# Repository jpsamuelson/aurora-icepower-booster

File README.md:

# Aurora DSP ICEpower Booster

**6-Channel Balanced Audio Interface** — Aurora FreeDSP → ICEpower Amplifier Modules

This board sits between an **Aurora FreeDSP DSP processor** and six **ICEpower Class-D amplifier modules**. It receives 6 balanced audio signals from the DSP, applies adjustable gain (0–11.3 dB), protects the signals, and outputs them as balanced XLR signals.

---

## Features

- **6 identical channels** — balanced XLR input & output
- **LM4562 low-noise dual op-amps** — THD+N 0.00003%, 2.7 nV/√Hz
- **0–11.3 dB gain** in 8 steps via 3-bit DIP switch per channel
- **100 ms power-on muting** — BSS138 MOSFET chain prevents pop noise
- **Remote enable** via 3.5mm jack (Aurora FreeDSP compatible)
- **Full ESD protection** — PESD5V0S1BL on all signal I/O, SMBJ15CA on remote
- **Isolated power supply** — TRACO TEL5-2422 DC/DC → ADP7118/ADP7182 LDOs (±11V)
- **JLCPCB-ready** — 2-layer FR-4, all components LCSC-available

---

## Specifications

| Parameter | Value |
|-----------|-------|
| Channels | 6 (identical) |
| Input | 6× XLR Female, Pin 2 = Hot, Pin 3 = Cold, Pin 1 = GND |
| Output | 6× XLR Male, Pin 2 = Hot, Pin 3 = Cold, Pin 1 = GND |
| Power Supply | 24V DC (Barrel Jack) |
| Op-Amp Supply | ±11V (low-noise LDO) |
| Gain Range | 0 dB to +11.3 dB (8 steps via DIP switch) |
| Input Impedance | ~10 kΩ balanced |
| Output Impedance | ~47Ω (series R) |
| Input CMRR | ~62 dB (4× 10kΩ 0.1% metal film) |
| SNR Target | > 100 dB |
| THD+N Target | < 0.01% @ 1 kHz |
| Remote Interface | KH-PJ-320EA-5P-SMT 3.5mm jack (Aurora FreeDSP Custom Out) |
| Manufacturing | JLCPCB, 2-Layer, FR-4, HASL, 145.6 × 200 mm |

---

## System Overview

```mermaid
graph LR
    DSP["Aurora FreeDSP\n(6× XLR Out)"]
    BOARD["Aurora DSP\nICEpower Booster"]
    AMP1["ICEpower #1"]
    AMP2["ICEpower #2"]
    AMP3["ICEpower #3"]
    AMP4["ICEpower #4"]
    AMP5["ICEpower #5"]
    AMP6["ICEpower #6"]
    PSU["24V DC\nPower Supply"]
    REMOTE["FreeDSP\nRemote Out"]

    DSP -->|"CH1 XLR Balanced"| BOARD
    DSP -->|"CH2 XLR Balanced"| BOARD
    DSP -->|"CH3 XLR Balanced"| BOARD
    DSP -->|"CH4 XLR Balanced"| BOARD
    DSP -->|"CH5 XLR Balanced"| BOARD
    DSP -->|"CH6 XLR Balanced"| BOARD
    PSU -->|"24V"| BOARD
    REMOTE -->|"3.5mm Enable"| BOARD
    BOARD -->|"CH1 +Gain"| AMP1
    BOARD -->|"CH2 +Gain"| AMP2
    BOARD -->|"CH3 +Gain"| AMP3
    BOARD -->|"CH4 +Gain"| AMP4
    BOARD -->|"CH5 +Gain"| AMP5
    BOARD -->|"CH6 +Gain"| AMP6
```

---

## Signal Chain Overview

All 6 channels are **identical**. Each channel consists of 5 stages:

```mermaid
flowchart LR
    XIN["XLR IN\nJ3–J8"]
    ESD1["ESD Protection\nInput"]
    EMI["EMI Filter\n47Ω + 100pF"]
    DC["DC Blocking\n2.2µF C0G"]
    DIFF["Diff Receiver\nLM4562 Unit A"]
    GAIN["Gain Stage\nLM4562 Unit B"]
    MUTE["Muting\nBSS138"]
    DRV["Balanced Driver\nLM4562 (2nd IC)"]
    ZOB["Zobel\n10Ω + 100nF"]
    ESD2["ESD Protection\nOutput"]
    XOUT["XLR OUT\nJ9–J14"]

    XIN --> ESD1 --> EMI --> DC --> DIFF --> GAIN --> MUTE --> DRV --> ZOB --> ESD2 --> XOUT
```

| Stage | Function | Key Components |
|-------|----------|---------------|
| 1. ESD & EMI Filter | Overvoltage protection + RF filtering | PESD5V0S1BL, 47Ω + 100pF, 2.2µF C0G DC blocking |
| 2. Diff Receiver | Balanced → single-ended, CMRR ~62 dB | LM4562 Unit A, 4× 10kΩ 0.1% |
| 3. Gain Stage | Inverting amp, 0–11.3 dB adjustable | LM4562 Unit B, DIP switch + 3 parallel R |
| 4. Muting | Power-on pop suppression, τ = 100 ms | BSS138 N-MOSFET, RC timing |
| 5. Balanced Driver | Single-ended → balanced output | LM4562 (buffer + inverter), 47Ω series R, Zobel network |

**→ [Full signal chain documentation with schematics and formulas](docs/signal-chain.md)**

---

## Gain Configuration

| SW Pos 1 (30kΩ) | SW Pos 2 (15kΩ) | SW Pos 3 (7.5kΩ) | Gain (dB) |
|:---:|:---:|:---:|---:|
| OFF | OFF | OFF | 0.0 dB |
| OFF | OFF | ON | +2.5 dB |
| OFF | ON | OFF | +4.4 dB |
| OFF | ON | ON | +6.0 dB |
| ON | OFF | OFF | +7.4 dB |
| ON | OFF | ON | +8.5 dB |
| ON | ON | OFF | +9.5 dB |
| ON | ON | ON | **+11.3 dB** |

$$G = \frac{R_f}{R_{in,eff}} \quad\text{with}\quad R_{in,eff} = R_{base} \parallel R_{pos1} \parallel R_{pos2} \parallel R_{pos3}$$

**→ [Full gain configuration details](docs/gain-configuration.md)**

---

## PCB Layout

| Parameter | Value |
|-----------|-------|
| Board Size | 145.6 × 200 mm |
| Layers | 2 (F.Cu + B.Cu) |
| Footprints | 269 |
| Nets | 135 in 5 net classes |
| Routing | Freerouting v2.0.1 — 1543 segments + 476 vias |
| GND Zones | F.Cu (solid connect) + B.Cu (thermal relief) |
| DRC | 0 Errors, 0 Unconnected, 198 Warnings (cosmetic) |

| Net Class | Nets | Track Width | Clearance |
|-----------|------|-------------|-----------|
| Default | 62 | 0.25 mm | 0.2 mm |
| Audio_Input | 30 | 0.3 mm | 0.25 mm |
| Audio_Output | 36 | 0.5 mm | 0.2 mm |
| Audio_Power | 0 | 0.8 mm | 0.2 mm |
| Power | 7 | 0.5 mm | 0.2 mm |

**→ [PCB layout details & DRC breakdown](docs/pcb-layout.md)**

---

## Manufacturing

Production files are ready in the `production/` directory:

- **Gerber + Drill** — `production/gerber/` (JLCPCB format, Protel extensions, tented vias)
- **BOM + Placement** — `production/assembly/` (JLCPCB SMT assembly format)

---

## Validation

| Method | Checks | Result |
|--------|--------|--------|
| **Method 1** — OrcadPCB2 netlist, component-centric | 85/85 | ✅ |
| **Method 2** — KiCad-native netlist, net-centric (pintype/pinfunction) | 177/177 | ✅ |

> All component references, net names, and pin assignments in the documentation were extracted directly from the verified KiCad netlist and are sufficient to fully rebuild the schematic without the `.kicad_sch` file.

---

## Documentation

| Document | Description |
|----------|-------------|
| **[Signal Chain](docs/signal-chain.md)** | Detailed 5-stage signal path with Mermaid diagrams, formulas, and per-stage component tables |
| **[Power Supply](docs/power-supply.md)** | DC/DC converter, LDOs, ferrite beads, decoupling architecture |
| **[Muting & Remote Control](docs/muting-and-remote.md)** | Remote enable logic, muting timing, SPDT switch modes |
| **[Gain Configuration](docs/gain-configuration.md)** | DIP switch table, gain formula, per-channel resistor mapping |
| **[Component Reference](docs/component-reference.md)** | Complete BOM with all 242 symbols: R, C, D, J, SW, Q, U, FB |
| **[Schematic Rebuild Guide](docs/schematic-rebuild-guide.md)** | Step-by-step wiring instructions + full 6-channel component mapping |
| **[PCB Layout](docs/pcb-layout.md)** | Net classes, DRC status, routing details |
| **[Research: Balanced Audio ICs](docs/research/balanced-audio-ic-comparison.md)** | THAT1240, DRV135, SSM2143, LM4562 comparison & JLCPCB availability |
| **[Research: THT Precision Components](docs/research/tht-precision-components.md)** | 0.1% resistors, C0G capacitors, THT sourcing guide |

---

## Project Structure

This project is **self-contained** — all footprints and 3D models are included locally.

```
├── aurora-dsp-icepower-booster.kicad_pro   # Project
├── aurora-dsp-icepower-booster.kicad_sch   # Schematic
├── aurora-dsp-icepower-booster.kicad_pcb   # PCB Layout
├── aurora-dsp-icepower-booster.kicad_sym   # Local symbols
├── aurora-dsp-icepower-booster.kicad_dru   # Custom design rules
├── footprints.pretty/                      # 21 footprints (local)
│   └── 3dshapes/                           # 19 STEP 3D models
├── production/
│   ├── gerber/                             # Manufacturing data
│   └── assembly/                           # BOM + placement data
├── docs/                                   # Detailed documentation
│   ├── signal-chain.md
│   ├── power-supply.md
│   ├── muting-and-remote.md
│   ├── gain-configuration.md
│   ├── component-reference.md
│   ├── schematic-rebuild-guide.md
│   ├── pcb-layout.md
│   └── research/
│       ├── balanced-audio-ic-comparison.md
│       └── tht-precision-components.md
└── scripts/                                # Build & validation scripts
```

---

*Schematic: KiCad 9 — `aurora-dsp-icepower-booster.kicad_sch`*
*Manufacturing: JLCPCB 2-Layer FR-4 HASL — Gerber files in `production/gerber/`*

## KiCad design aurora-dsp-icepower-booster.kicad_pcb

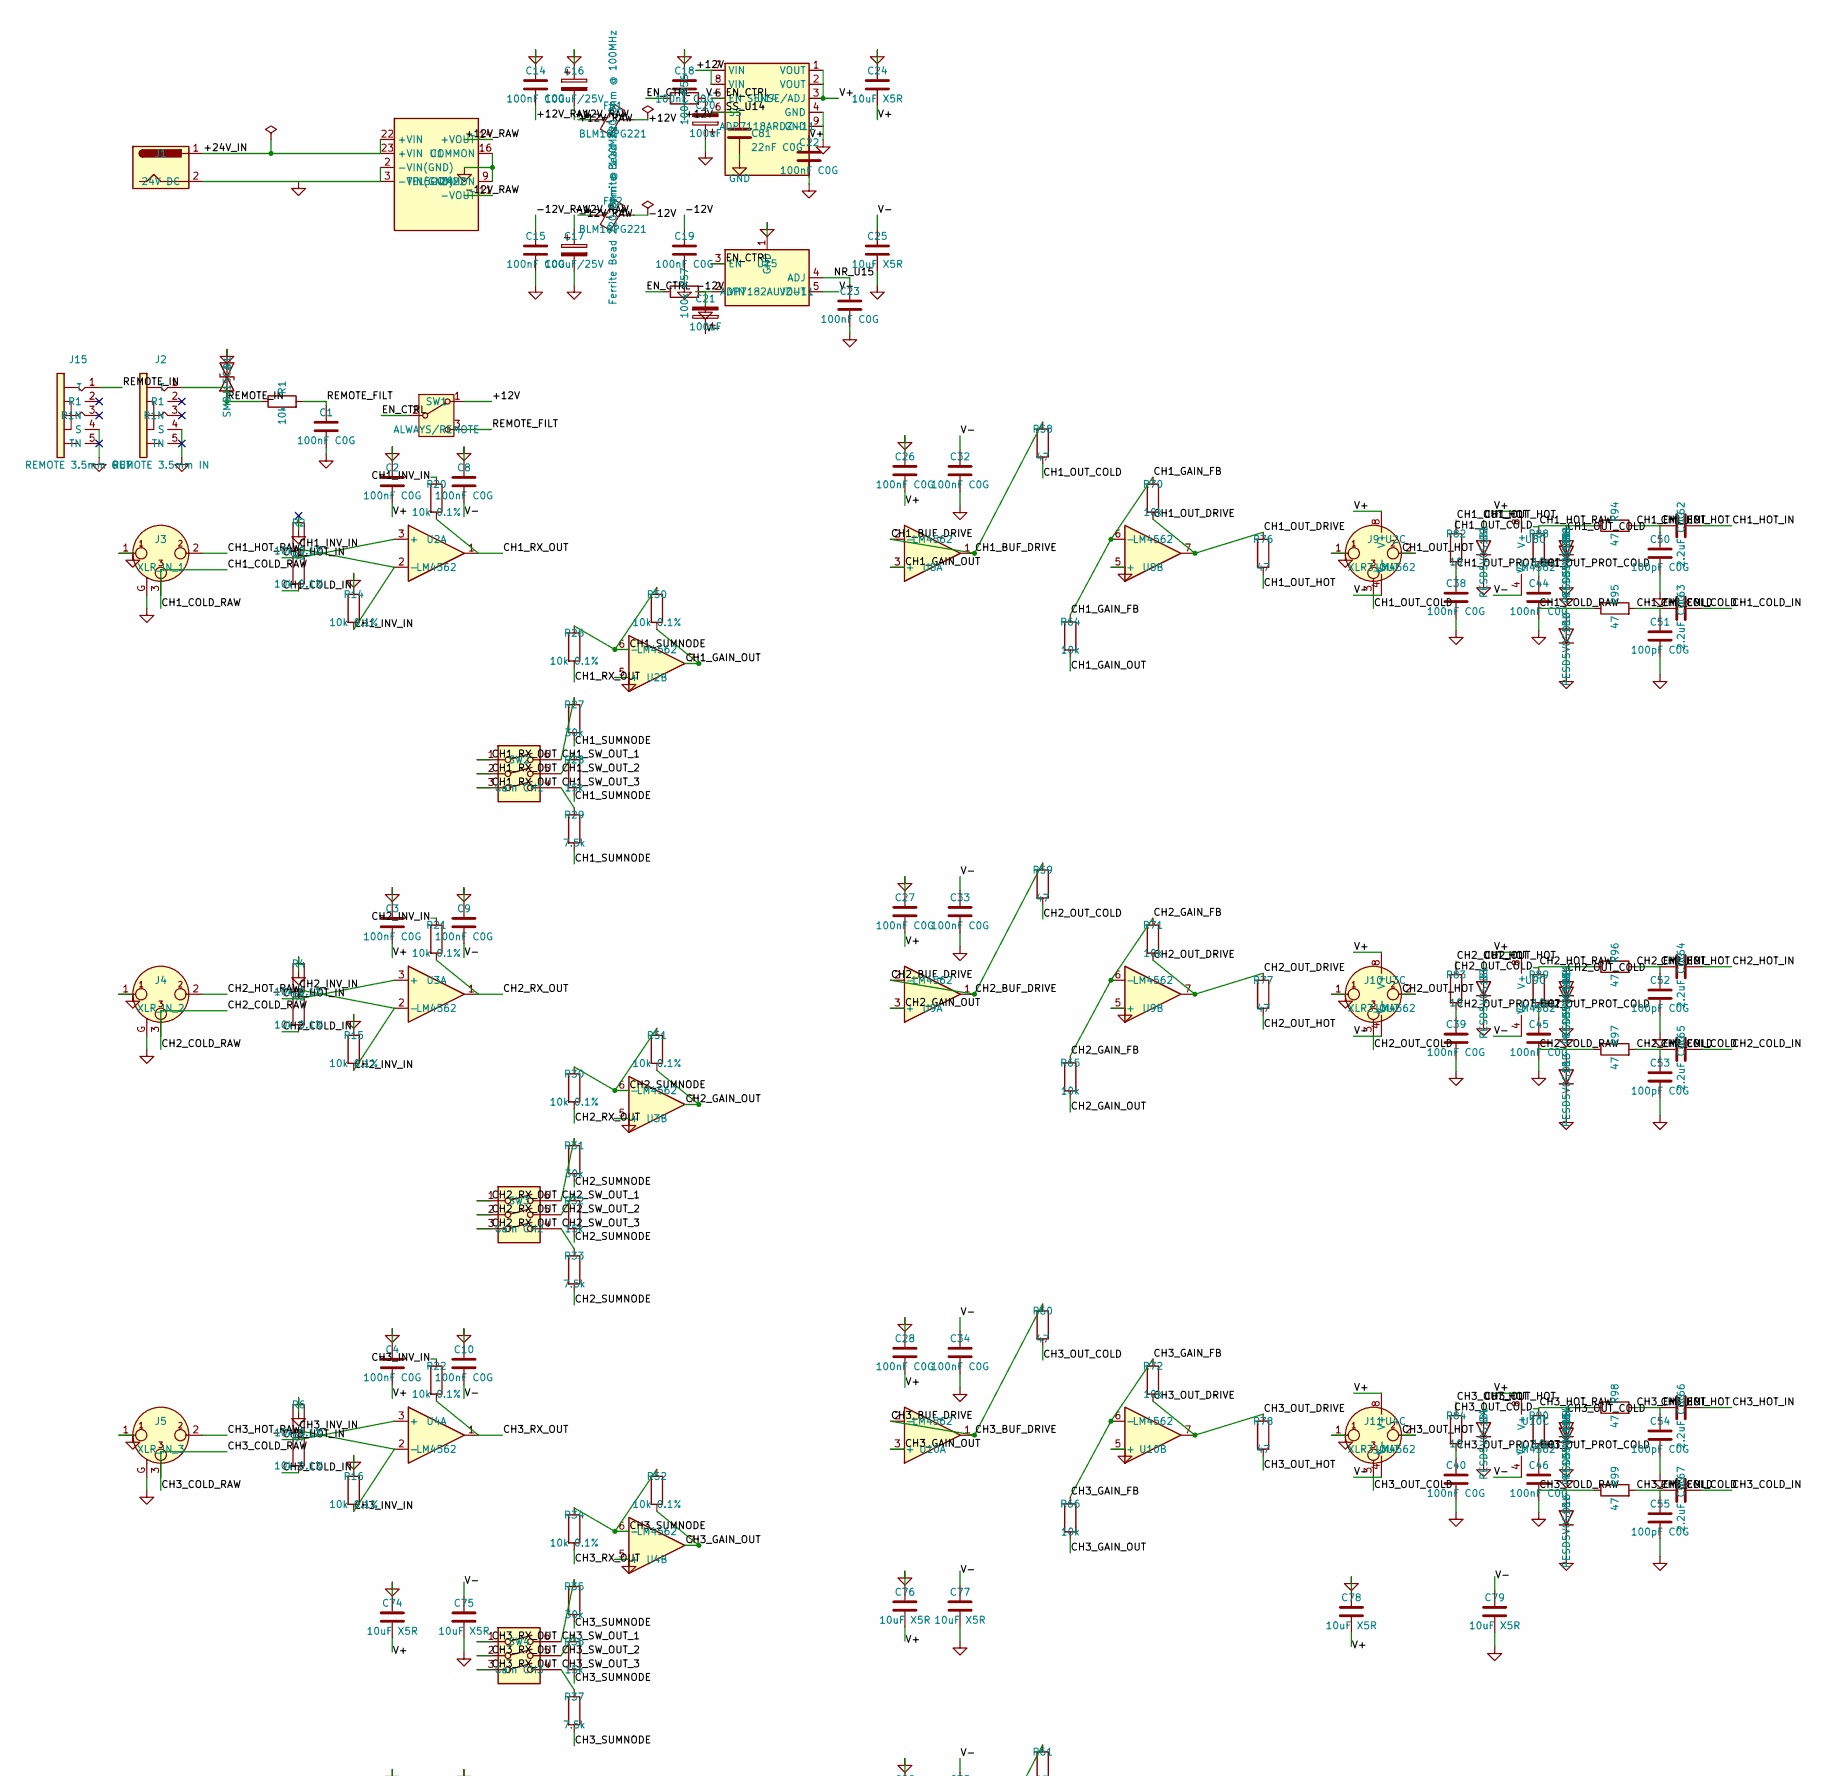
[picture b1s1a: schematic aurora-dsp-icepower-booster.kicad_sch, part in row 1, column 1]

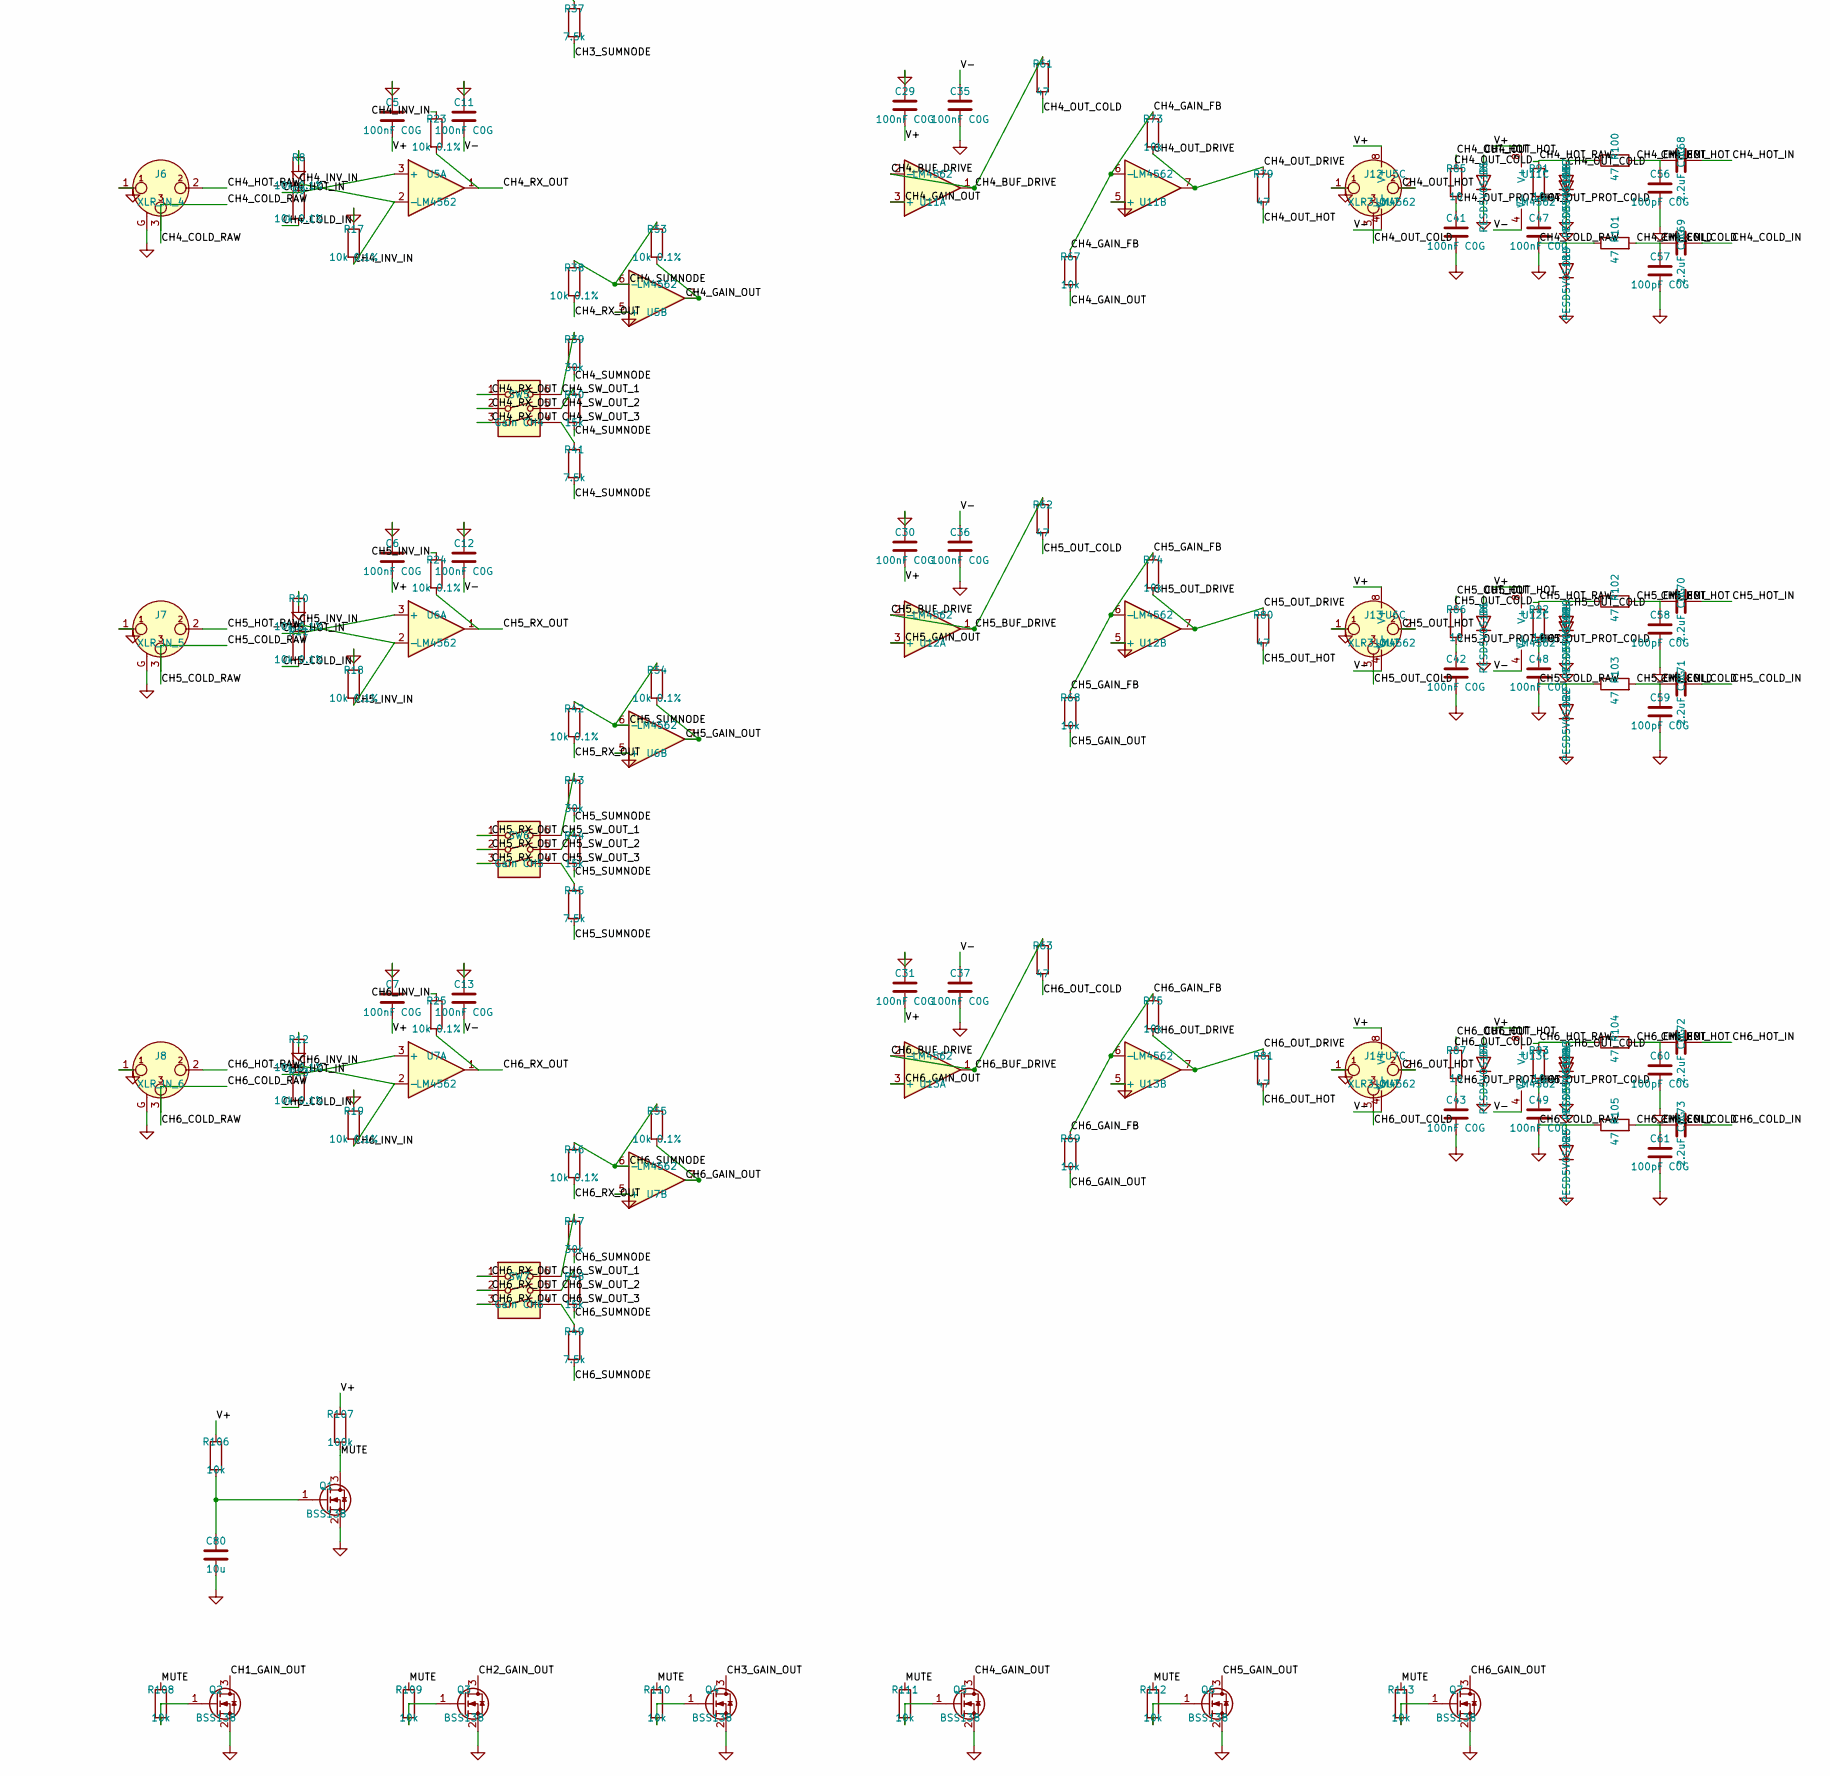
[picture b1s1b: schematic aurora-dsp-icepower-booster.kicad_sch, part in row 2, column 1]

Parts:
C1, C2, C3, C4, C5, C6, C7, C8, C9, C10, C11, C12, C13, C14, C15, C18, C19, C22, C23, C26, C27, C28, C29, C30, C31, C32, C33, C34, C35, C36, C37, C38, C39, C40, C41, C42, C43, C44, C45, C46, C47, C48, C49: 100nF C0G; C_0805_2012Metric
C16, C17: 100uF/25V; C_1210_3225Metric
C20, C21: 100uF; C_1210_3225Metric
C24, C25, C74, C75, C76, C77, C78, C79: 10uF X5R; C_0805_2012Metric
C50, C51, C52, C53, C54, C55, C56, C57, C58, C59, C60, C61: 100pF C0G; C_0805_2012Metric
C62, C63, C64, C65, C66, C67, C68, C69, C70, C71, C72, C73: 2.2uF C0G; C_1206_3216Metric
C80: 10u; C_0805_2012Metric
C81: 22nF C0G; C_0402_1005Metric
D1: SMBJ15CA; D_SMB
D2, D3, D4, D5, D6, D7, D8, D9, D10, D11, D12, D13, D14, D15, D16, D17, D18, D19, D20, D21, D22, D23, D24, D25: PESD5V0S1BL; D_SOD-323
FB1, FB2: BLM18PG221; L_0805_2012Metric
J1: 24V DC; BarrelJack_Horizontal
J2: REMOTE 3.5mm IN; AUDIO-SMD_KH-PJ-320EA-5P-SMT; LCSC C5123132
J3: XLR_IN_1; Jack_XLR_Neutrik_NC3FBH2_Horizontal
J4: XLR_IN_2; Jack_XLR_Neutrik_NC3FBH2_Horizontal
J5: XLR_IN_3; Jack_XLR_Neutrik_NC3FBH2_Horizontal
J6: XLR_IN_4; Jack_XLR_Neutrik_NC3FBH2_Horizontal
J7: XLR_IN_5; Jack_XLR_Neutrik_NC3FBH2_Horizontal
J8: XLR_IN_6; Jack_XLR_Neutrik_NC3FBH2_Horizontal
J9, J10, J11, J12, J13, J14: XLR3_OUT; Jack_XLR_Neutrik_NC3MBH_Horizontal
J15: REMOTE 3.5mm OUT; AUDIO-SMD_KH-PJ-320EA-5P-SMT; LCSC C5123132
Q1, Q2, Q3, Q4, Q5, Q6, Q7: BSS138; SOT-23
R1, R64, R65, R66, R67, R68, R69, R70, R71, R72, R73, R74, R75, R106, R108, R109, R110, R111, R112, R113: 10k; R_0805_2012Metric
R2, R3, R4, R5, R6, R7, R8, R9, R10, R11, R12, R13, R14, R15, R16, R17, R18, R19, R20, R21, R22, R23, R24, R25, R26, R30, R34, R38, R42, R46, R50, R51, R52, R53, R54, R55: 10k 0.1%; R_0805_2012Metric
R27, R31, R35, R39, R43, R47: 30k; R_0805_2012Metric
R28, R32, R36, R40, R44, R48: 15k; R_0805_2012Metric
R29, R33, R37, R41, R45, R49: 7.5k; R_0805_2012Metric
R56, R57, R107: 100k; R_0805_2012Metric
R58, R59, R60, R61, R62, R63, R76, R77, R78, R79, R80, R81, R94, R95, R96, R97, R98, R99, R100, R101, R102, R103, R104, R105: 47; R_0805_2012Metric
R82, R83, R84, R85, R86, R87, R88, R89, R90, R91, R92, R93: 10; R_0805_2012Metric
SW1: ALWAYS/REMOTE; SW_E-Switch_EG1224_SPDT_Angled
SW2: Gain CH1; SW_DIP_SPSTx03_Slide_Omron_A6S-310x_W8.9mm_P2.54mm
SW3: Gain CH2; SW_DIP_SPSTx03_Slide_Omron_A6S-310x_W8.9mm_P2.54mm
SW4: Gain CH3; SW_DIP_SPSTx03_Slide_Omron_A6S-310x_W8.9mm_P2.54mm
SW5: Gain CH4; SW_DIP_SPSTx03_Slide_Omron_A6S-310x_W8.9mm_P2.54mm
SW6: Gain CH5; SW_DIP_SPSTx03_Slide_Omron_A6S-310x_W8.9mm_P2.54mm
SW7: Gain CH6; SW_DIP_SPSTx03_Slide_Omron_A6S-310x_W8.9mm_P2.54mm
U1: TEL5-2422; TEL5_DUAL_TRP
U2, U3, U4, U5, U6, U7, U8, U9, U10, U11, U12, U13: LM4562; SOIC-8_3.9x4.9mm_P1.27mm
U14: ADP7118ARDZ-11; SOIC127P600X175-9N
U15: ADP7182AUJZ-11; SOT-23-5

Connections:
/+12V: C18.2, FB1.2, SW1.1 (A), U14.7 (VIN), U14.8 (VIN)
/+12V_RAW: C14.2, C16.2, FB1.1, U1.14 (+VOUT)
/+24V_IN: J1.1, U1.22 (+VIN), U1.23 (+VIN)
/-12V: C19.1, FB2.2, U15.2 (VIN)
/-12V_RAW: C15.1, C17.1, FB2.1, U1.11 (-VOUT)
/CH1_BUF_DRIVE: R58.1, U8.1, U8.2 (-)
/CH1_COLD_IN: C63.2, R3.2
/CH1_COLD_RAW: D10.2 (A), J3.3, R95.1
/CH1_EMI_COLD: C51.1, C63.1, R95.2
/CH1_EMI_HOT: C50.1, C62.1, R94.2
/CH1_GAIN_FB: R64.1, R70.1, U8.6 (-)
/CH1_GAIN_OUT: Q2.3 (D), R50.2, R64.2, U2.7, U8.3 (+)
/CH1_HOT_IN: C62.2, R2.2, U2.3 (+)
/CH1_HOT_RAW: D8.2 (A), J3.2, R94.1
/CH1_INV_IN: R3.1, R14.2, R20.1, U2.2 (-)
/CH1_OUT_COLD: D9.2 (A), J9.3, R58.2, R88.1
/CH1_OUT_DRIVE: R70.2, R76.1, U8.7
/CH1_OUT_HOT: D2.2 (A), J9.2, R76.2, R82.1
/CH1_OUT_PROT_COLD: C44.1, R88.2
/CH1_OUT_PROT_HOT: C38.1, R82.2
/CH1_RX_OUT: R20.2, R26.2, SW2.1, SW2.2, SW2.3, U2.1
/CH1_SUMNODE: R26.1, R27.2, R28.2, R29.2, R50.1, U2.6 (-)
/CH1_SW_OUT_1: R27.1, SW2.6
/CH1_SW_OUT_2: R28.1, SW2.5
/CH1_SW_OUT_3: R29.1, SW2.4
/CH2_BUF_DRIVE: R59.1, U9.1, U9.2 (-)
/CH2_COLD_IN: C65.2, R5.2
/CH2_COLD_RAW: D13.2 (A), J4.3, R97.1
/CH2_EMI_COLD: C53.1, C65.1, R97.2
/CH2_EMI_HOT: C52.1, C64.1, R96.2
/CH2_GAIN_FB: R65.1, R71.1, U9.6 (-)
/CH2_GAIN_OUT: Q3.3 (D), R51.2, R65.2, U3.7, U9.3 (+)
/CH2_HOT_IN: C64.2, R4.2, U3.3 (+)
/CH2_HOT_RAW: D11.2 (A), J4.2, R96.1
/CH2_INV_IN: R5.1, R15.2, R21.1, U3.2 (-)
/CH2_OUT_COLD: D12.2 (A), J10.3, R59.2, R89.1
/CH2_OUT_DRIVE: R71.2, R77.1, U9.7
/CH2_OUT_HOT: D3.2 (A), J10.2, R77.2, R83.1
/CH2_OUT_PROT_COLD: C45.1, R89.2
/CH2_OUT_PROT_HOT: C39.1, R83.2
/CH2_RX_OUT: R21.2, R30.2, SW3.1, SW3.2, SW3.3, U3.1
/CH2_SUMNODE: R30.1, R31.2, R32.2, R33.2, R51.1, U3.6 (-)
/CH2_SW_OUT_1: R31.1, SW3.6
/CH2_SW_OUT_2: R32.1, SW3.5
/CH2_SW_OUT_3: R33.1, SW3.4
/CH3_BUF_DRIVE: R60.1, U10.1, U10.2 (-)
/CH3_COLD_IN: C67.2, R7.2
/CH3_COLD_RAW: D16.2 (A), J5.3, R99.1
/CH3_EMI_COLD: C55.1, C67.1, R99.2
/CH3_EMI_HOT: C54.1, C66.1, R98.2
/CH3_GAIN_FB: R66.1, R72.1, U10.6 (-)
/CH3_GAIN_OUT: Q4.3 (D), R52.2, R66.2, U4.7, U10.3 (+)
/CH3_HOT_IN: C66.2, R6.2, U4.3 (+)
/CH3_HOT_RAW: D14.2 (A), J5.2, R98.1
/CH3_INV_IN: R7.1, R16.2, R22.1, U4.2 (-)
/CH3_OUT_COLD: D15.2 (A), J11.3, R60.2, R90.1
/CH3_OUT_DRIVE: R72.2, R78.1, U10.7
/CH3_OUT_HOT: D4.2 (A), J11.2, R78.2, R84.1
/CH3_OUT_PROT_COLD: C46.1, R90.2
/CH3_OUT_PROT_HOT: C40.1, R84.2
/CH3_RX_OUT: R22.2, R34.2, SW4.1, SW4.2, SW4.3, U4.1
/CH3_SUMNODE: R34.1, R35.2, R36.2, R37.2, R52.1, U4.6 (-)
/CH3_SW_OUT_1: R35.1, SW4.6
/CH3_SW_OUT_2: R36.1, SW4.5
/CH3_SW_OUT_3: R37.1, SW4.4
/CH4_BUF_DRIVE: R61.1, U11.1, U11.2 (-)
/CH4_COLD_IN: C69.2, R9.2
/CH4_COLD_RAW: D19.2 (A), J6.3, R101.1
/CH4_EMI_COLD: C57.1, C69.1, R101.2
/CH4_EMI_HOT: C56.1, C68.1, R100.2
/CH4_GAIN_FB: R67.1, R73.1, U11.6 (-)
/CH4_GAIN_OUT: Q5.3 (D), R53.2, R67.2, U5.7, U11.3 (+)
/CH4_HOT_IN: C68.2, R8.2, U5.3 (+)
/CH4_HOT_RAW: D17.2 (A), J6.2, R100.1
/CH4_INV_IN: R9.1, R17.2, R23.1, U5.2 (-)
/CH4_OUT_COLD: D18.2 (A), J12.3, R61.2, R91.1
/CH4_OUT_DRIVE: R73.2, R79.1, U11.7
/CH4_OUT_HOT: D5.2 (A), J12.2, R79.2, R85.1
/CH4_OUT_PROT_COLD: C47.1, R91.2
/CH4_OUT_PROT_HOT: C41.1, R85.2
/CH4_RX_OUT: R23.2, R38.2, SW5.1, SW5.2, SW5.3, U5.1
/CH4_SUMNODE: R38.1, R39.2, R40.2, R41.2, R53.1, U5.6 (-)
/CH4_SW_OUT_1: R39.1, SW5.6
/CH4_SW_OUT_2: R40.1, SW5.5
/CH4_SW_OUT_3: R41.1, SW5.4
/CH5_BUF_DRIVE: R62.1, U12.1, U12.2 (-)
/CH5_COLD_IN: C71.2, R11.2
/CH5_COLD_RAW: D22.2 (A), J7.3, R103.1
/CH5_EMI_COLD: C59.1, C71.1, R103.2
/CH5_EMI_HOT: C58.1, C70.1, R102.2
/CH5_GAIN_FB: R68.1, R74.1, U12.6 (-)
/CH5_GAIN_OUT: Q6.3 (D), R54.2, R68.2, U6.7, U12.3 (+)
/CH5_HOT_IN: C70.2, R10.2, U6.3 (+)
/CH5_HOT_RAW: D20.2 (A), J7.2, R102.1
/CH5_INV_IN: R11.1, R18.2, R24.1, U6.2 (-)
/CH5_OUT_COLD: D21.2 (A), J13.3, R62.2, R92.1
/CH5_OUT_DRIVE: R74.2, R80.1, U12.7
/CH5_OUT_HOT: D6.2 (A), J13.2, R80.2, R86.1
/CH5_OUT_PROT_COLD: C48.1, R92.2
/CH5_OUT_PROT_HOT: C42.1, R86.2
/CH5_RX_OUT: R24.2, R42.2, SW6.1, SW6.2, SW6.3, U6.1
/CH5_SUMNODE: R42.1, R43.2, R44.2, R45.2, R54.1, U6.6 (-)
/CH5_SW_OUT_1: R43.1, SW6.6
/CH5_SW_OUT_2: R44.1, SW6.5
/CH5_SW_OUT_3: R45.1, SW6.4
/CH6_BUF_DRIVE: R63.1, U13.1, U13.2 (-)
/CH6_COLD_IN: C73.2, R13.2
/CH6_COLD_RAW: D25.2 (A), J8.3, R105.1
/CH6_EMI_COLD: C61.1, C73.1, R105.2
/CH6_EMI_HOT: C60.1, C72.1, R104.2
/CH6_GAIN_FB: R69.1, R75.1, U13.6 (-)
/CH6_GAIN_OUT: Q7.3 (D), R55.2, R69.2, U7.7, U13.3 (+)
/CH6_HOT_IN: C72.2, R12.2, U7.3 (+)
/CH6_HOT_RAW: D23.2 (A), J8.2, R104.1
/CH6_INV_IN: R13.1, R19.2, R25.1, U7.2 (-)
/CH6_OUT_COLD: D24.2 (A), J14.3, R63.2, R93.1
/CH6_OUT_DRIVE: R75.2, R81.1, U13.7
/CH6_OUT_HOT: D7.2 (A), J14.2, R81.2, R87.1
/CH6_OUT_PROT_COLD: C49.1, R93.2
/CH6_OUT_PROT_HOT: C43.1, R87.2
/CH6_RX_OUT: R25.2, R46.2, SW7.1, SW7.2, SW7.3, U7.1
/CH6_SUMNODE: R46.1, R47.2, R48.2, R49.2, R55.1, U7.6 (-)
/CH6_SW_OUT_1: R47.1, SW7.6
/CH6_SW_OUT_2: R48.1, SW7.5
/CH6_SW_OUT_3: R49.1, SW7.4
/EN_CTRL: R56.1, R57.1, SW1.2 (B), U14.5 (EN), U15.3 (EN)
/MUTE: Q1.3 (D), R107.2, R108.1, R109.1, R110.1, R111.1, R112.1, R113.1
/NR_U15: C23.1, U15.4 (ADJ)
/REMOTE_FILT: C1.1, R1.2, SW1.3 (C)
/REMOTE_IN: D1.1 (A1), J2.1 (T), J15.1 (T), R1.1
/SS_U14: C81.1, U14.6 (SS)
/V+: C2.2, C3.2, C4.2, C5.2, C6.2, C7.2, C20.2, C22.1, C24.2, C26.2, C27.2, C28.2, C29.2, C30.2, C31.2, C74.2, C76.2, C78.2, R56.2, R106.1, R107.1, U2.8 (V+), U3.8 (V+), U4.8 (V+), U5.8 (V+), U6.8 (V+), U7.8 (V+), U8.8 (V+), U9.8 (V+), U10.8 (V+), U11.8 (V+), U12.8 (V+), U13.8 (V+), U14.1 (VOUT), U14.2 (VOUT), U14.3 (SENSE/ADJ)
/V-: C8.2, C9.2, C10.2, C11.2, C12.2, C13.2, C21.1, C25.1, C32.1, C33.1, C34.1, C35.1, C36.1, C37.1, C75.1, C77.1, C79.1, U2.4 (V-), U3.4 (V-), U4.4 (V-), U5.4 (V-), U6.4 (V-), U7.4 (V-), U8.4 (V-), U9.4 (V-), U10.4 (V-), U11.4 (V-), U12.4 (V-), U13.4 (V-), U15.5 (VOUT)
GND: C1.2, C2.1, C3.1, C4.1, C5.1, C6.1, C7.1, C8.1, C9.1, C10.1, C11.1, C12.1, C13.1, C14.1, C15.2, C16.1, C17.2, C18.1, C19.2, C20.1, C21.2, C22.2, C23.2, C24.1, C25.2, C26.1, C27.1, C28.1, C29.1, C30.1, C31.1, C32.2, C33.2, C34.2, C35.2, C36.2, C37.2, C38.2, C39.2, C40.2, C41.2, C42.2, C43.2, C44.2, C45.2, C46.2, C47.2, C48.2, C49.2, C50.2, C51.2, C52.2, C53.2, C54.2, C55.2, C56.2, C57.2, C58.2, C59.2, C60.2, C61.2, C74.1, C75.2, C76.1, C77.2, C78.1, C79.2, C80.2, C81.2, D1.2 (A2), D2.1 (K), D3.1 (K), D4.1 (K), D5.1 (K), D6.1 (K), D7.1 (K), D8.1 (K), D9.1 (K), D10.1 (K), D11.1 (K), D12.1 (K), D13.1 (K), D14.1 (K), D15.1 (K), D16.1 (K), D17.1 (K), D18.1 (K), D19.1 (K), D20.1 (K), D21.1 (K), D22.1 (K), D23.1 (K), D24.1 (K), D25.1 (K), J1.2, J2.4 (S), J3.1, J3.G, J4.1, J4.G, J5.1, J5.G, J6.1, J6.G, J7.1, J7.G, J8.1, J8.G, J9.1, J10.1, J11.1, J12.1, J13.1, J14.1, J15.4 (S), Q1.2 (S), Q2.2 (S), Q3.2 (S), Q4.2 (S), Q5.2 (S), Q6.2 (S), Q7.2 (S), R2.1, R4.1, R6.1, R8.1, R10.1, R12.1, R14.1, R15.1, R16.1, R17.1, R18.1, R19.1, R57.2, U1.2 (-VIN(GND)), U1.3 (-VIN(GND)), U1.9 (COMMON), U1.16 (COMMON), U2.5 (+), U3.5 (+), U4.5 (+), U5.5 (+), U6.5 (+), U7.5 (+), U8.5 (+), U9.5 (+), U10.5 (+), U11.5 (+), U12.5 (+), U13.5 (+), U14.4 (GND), U14.9 (GND), U15.1 (GND)
unnamed: C80.1, Q1.1 (G), R106.2
unnamed: Q2.1 (G), R108.2
unnamed: Q3.1 (G), R109.2
unnamed: Q4.1 (G), R110.2
unnamed: Q5.1 (G), R111.2
unnamed: Q6.1 (G), R112.2
unnamed: Q7.1 (G), R113.2

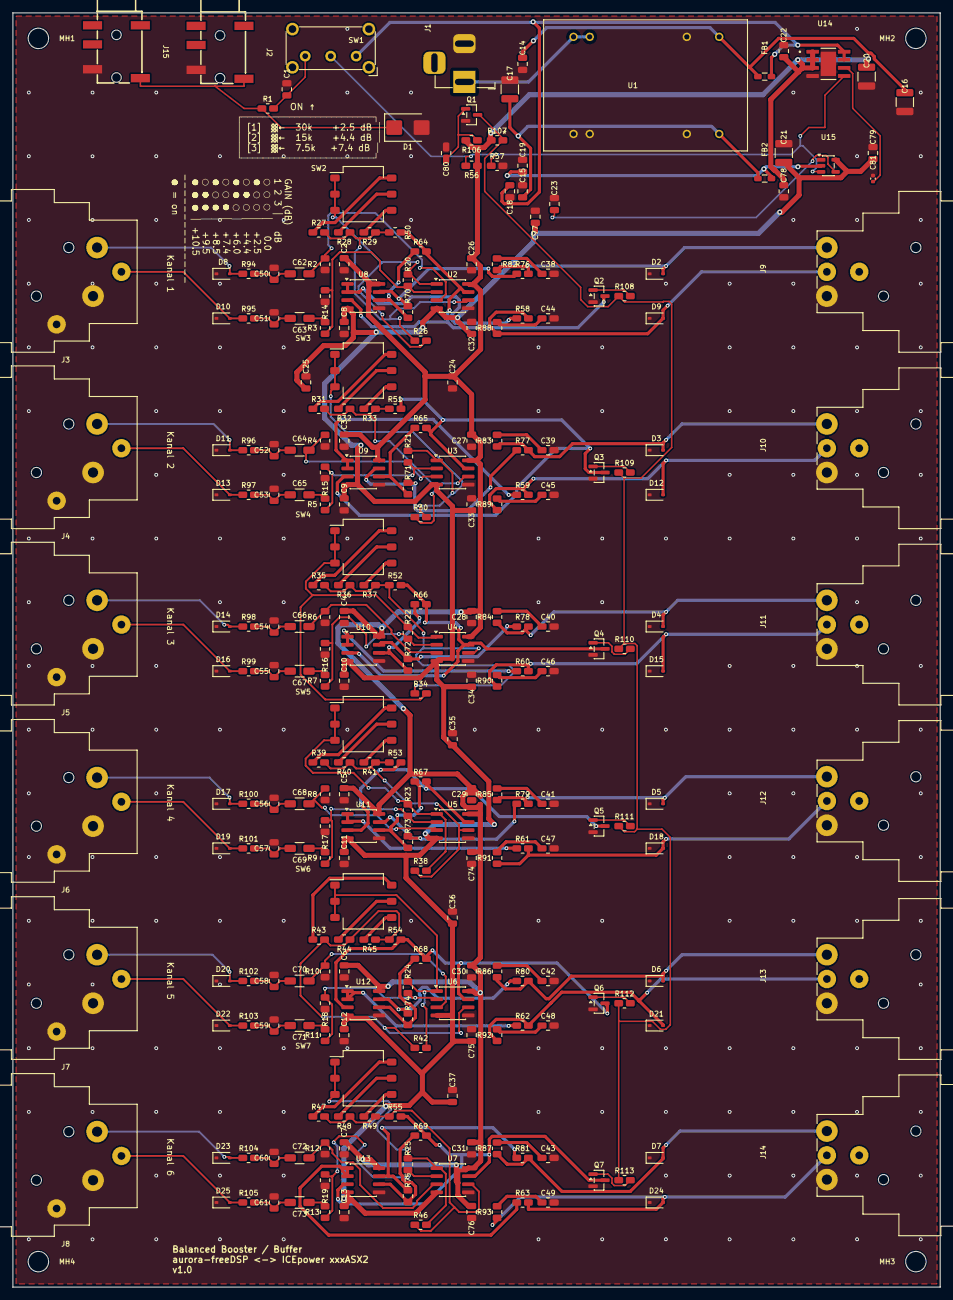
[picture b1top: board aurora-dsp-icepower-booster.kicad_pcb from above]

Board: 2 copper layers, 145.6 x 200.0 mm, 269 parts (0 on the bottom side), 141 nets.

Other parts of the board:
MH1, MH2, MH3, MH4: MountingHole; MountingHole_3.2mm_M3

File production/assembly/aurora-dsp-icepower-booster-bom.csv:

"Reference","Value","Footprint","QUANTITY"
"C1-C15,C18,C19,C22,C23,C26-C49","100nF C0G","Capacitor_SMD:C_0805_2012Metric","43"
"C16,C17","100uF/25V","Capacitor_SMD:C_1210_3225Metric","2"
"C20,C21","100uF","Capacitor_SMD:C_1210_3225Metric","2"
"C24,C25,C74-C79","10uF X5R","Capacitor_SMD:C_0805_2012Metric","8"
"C50-C61","100pF C0G","Capacitor_SMD:C_0805_2012Metric","12"
"C62-C73","2.2uF C0G","Capacitor_SMD:C_1206_3216Metric","12"
"C80","10u","Capacitor_SMD:C_0805_2012Metric","1"
"C81","22nF C0G","Capacitor_SMD:C_0402_1005Metric","1"
"D1","SMBJ15CA","Diode_SMD:D_SMB","1"
"D2-D25","PESD5V0S1BL","Diode_SMD:D_SOD-323","24"
"FB1,FB2","BLM18PG221","Inductor_SMD:L_0805_2012Metric","2"
"J1","24V DC","Connector_BarrelJack:BarrelJack_Horizontal","1"
"J2","REMOTE 3.5mm","Connector_Audio:Jack_3.5mm_Lumberg_1503_02_Horizontal","1"
"J3","XLR_IN_1","Connector_Audio:Jack_XLR_Neutrik_NC3FBH2_Horizontal","1"
"J4","XLR_IN_2","Connector_Audio:Jack_XLR_Neutrik_NC3FBH2_Horizontal","1"
"J5","XLR_IN_3","Connector_Audio:Jack_XLR_Neutrik_NC3FBH2_Horizontal","1"
"J6","XLR_IN_4","Connector_Audio:Jack_XLR_Neutrik_NC3FBH2_Horizontal","1"
"J7","XLR_IN_5","Connector_Audio:Jack_XLR_Neutrik_NC3FBH2_Horizontal","1"
"J8","XLR_IN_6","Connector_Audio:Jack_XLR_Neutrik_NC3FBH2_Horizontal","1"
"J9-J14","XLR3_OUT","Connector_Audio:Jack_XLR_Neutrik_NC3MBH_Horizontal","6"
"Q1-Q7","BSS138","Package_TO_SOT_SMD:SOT-23","7"
"R1,R64-R75,R106,R108-R113","10k","Resistor_SMD:R_0805_2012Metric","20"
"R2-R26,R30,R34,R38,R42,R46,R50-R55","10k 0.1%","Resistor_SMD:R_0805_2012Metric","36"
"R27,R31,R35,R39,R43,R47","30k","Resistor_SMD:R_0805_2012Metric","6"
"R28,R32,R36,R40,R44,R48","15k","Resistor_SMD:R_0805_2012Metric","6"
"R29,R33,R37,R41,R45,R49","7.5k","Resistor_SMD:R_0805_2012Metric","6"
"R56,R57,R107","100k","Resistor_SMD:R_0805_2012Metric","3"
"R58-R63,R76-R81,R94-R105","47","Resistor_SMD:R_0805_2012Metric","24"
"R82-R93","10","Resistor_SMD:R_0805_2012Metric","12"
"SW1","ALWAYS/REMOTE","Button_Switch_THT:SW_E-Switch_EG1224_SPDT_Angled","1"
"SW2","Gain CH1","Button_Switch_SMD:SW_DIP_SPSTx03_Slide_Omron_A6S-310x_W8.9mm_P2.54mm","1"
"SW3","Gain CH2","Button_Switch_SMD:SW_DIP_SPSTx03_Slide_Omron_A6S-310x_W8.9mm_P2.54mm","1"
"SW4","Gain CH3","Button_Switch_SMD:SW_DIP_SPSTx03_Slide_Omron_A6S-310x_W8.9mm_P2.54mm","1"
"SW5","Gain CH4","Button_Switch_SMD:SW_DIP_SPSTx03_Slide_Omron_A6S-310x_W8.9mm_P2.54mm","1"
"SW6","Gain CH5","Button_Switch_SMD:SW_DIP_SPSTx03_Slide_Omron_A6S-310x_W8.9mm_P2.54mm","1"
"SW7","Gain CH6","Button_Switch_SMD:SW_DIP_SPSTx03_Slide_Omron_A6S-310x_W8.9mm_P2.54mm","1"
"U1","TEL5-2422","project:TEL5_DUAL_TRP","1"
"U2-U13","LM4562","Package_SO:SOIC-8_3.9x4.9mm_P1.27mm","12"
"U14","ADP7118ARDZ-11","project:SOIC127P600X175-9N","1"
"U15","ADP7182AUJZ-11","Package_TO_SOT_SMD:SOT-23-5","1"

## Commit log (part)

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2026-03-12 feat(vscode): 🎉 add MCP server configuration for KiCAD
    - Introduced a new configuration file `.vscode/mcp.json` to set up the MCP server for KiCAD.
    - The configuration specifies the command to run the server and sets necessary environment variables:
    * `PYTHONPATH` for Python package location.
    * `LOG_LEVEL` to control logging verbosity.
    * `KICAD_AUTO_LAUNCH` to manage automatic launching behavior.
2026-03-12 feat(symbols): ✨ Add TEL5-2422 DC/DC converter symbol and library entry
    * Introduced a new symbol for the TRACO TEL5-2422 isolated DC/DC converter.
    * Added properties including Reference, Value, Footprint, Datasheet, and Description.
    * Created a corresponding symbol library entry in `sym-lib-table` for easy access.
2026-03-13 feat(aurora-dsp-icepower-booster): 🎛️ update audio jack component and metadata
    * Changed the footprint of `J14` from `Connector_Audio:AudioJack2_Ground_Switch_Lumberg_1503_09` to `Connector_Audio:Jack_3.5mm_Lumberg_1503_02_Horizontal`.
    * Updated the `libsource` and `fields` for `J14` to reflect the new audio jack specifications.
    * Adjusted the pin references for `J14` in the net connections to match the new footprint.
    * Added a new library part for `AudioJack2` with relevant fields and pins.
2026-03-13 chore: 🔄 update code structure for better maintainability
    * Refactored multiple code sections to improve readability.
    * Removed redundant code blocks to streamline functionality.
    * Enhanced comments for clarity on complex logic.
2026-03-15 chore: remove tracked .bak backup files
    Backup files are now replaced by git commits.
    Deleted: bak_pre_phase6f_test, bak_pre_phase6g, bak_pre_phase6g_v2
2026-03-15 SW7: Pin Header -> EG1224 SPDT Rocker Switch, Board 200x220mm, J13/SW7/J14 zentriert
    - SW7 Footprint: PinHeader_1x03 -> SW_E-Switch_EG1224_SPDT_Angled
    - SW7 rotiert 180°, ragt 10mm über Oberkante hinaus (Kippschalter)
    - J13 (Barrel Jack) bei x=80, ragt 9mm über Oberkante
    - J14 (3.5mm Remote) bei x=120, ragt 4.5mm über Oberkante
    - Board von 200x200mm auf 200x220mm vergrößert (+20mm Y)
    - Alle Bauteile 10mm nach unten verschoben (mehr Platz für PSU-Bereich)
2026-03-15 PCB: Alle Tracks/Vias gelöscht + Speaker-Netzklasse hinzugefügt
    - 1043 Tracks + 194 Vias entfernt (clean slate für Routing-Neubeginn)
    - Speaker-Netzklasse: 1.5mm Track, 0.8mm Via, 0.3mm Clearance
    - CHx_EMI_HOT/COLD von Audio_Input auf Speaker umgestellt
    - DRC: 0 Shorts, 0 Dangles, 479 Unconnected (erwartungsgemäß)
2026-03-15 Signal routing v13c: 247 safe stubs, 70 shorts, 32 crossings, 165 signal gaps remaining
    - v6 base: pad-avoidance shifting + B.Cu jumpers at crossings
    - Two-pass: route all nets first, then fix gaps with safe F.Cu stubs
    - Safe stubs: only placed if no pad collision AND no track crossing
    - 429 gaps detected, 247 safely fixed, 182 skipped (need manual routing)
    - GND unconnected (132) will be fixed by copper pour
    - Remaining 165 signal gaps for manual completion in KiCad
2026-03-15 Phase 2: 0 shorts, 0 crossings (54 tracks + 13 vias entfernt)
2026-03-15 Phase 4: 49 signal gaps geroutet, 0 errors (259 unconnected verbleiben)
2026-03-16 Phase 6a: 275 dangling stubs entfernt, 0 DRC errors
2026-03-16 Phase 6d: Guard-Trace-Enden mit GND-Vias verbunden, DRC Cleanup
    - 73 dangling Guard-Trace-Enden mit nahen GND-Vias verbunden
    - track_dangling: 83 → 49, via_dangling: 97 → 80
    - Unconnected: 150 → 132
    - F.Cu tracks: 1012 → 1085
    - 0 DRC errors, 199 warnings (nur kosmetisch)
2026-03-16 Phase 7c: Decoupling caps repositioned to <2mm from IC power pins
    - C1-C24: Moved from 5-9mm to 1.55mm from LM4562 V+/V- pins
    - C37/C38: Moved from 7-9mm to 1.55mm from LDO output pins
    - 65 dangling trace stubs cleaned up
    - All 26 caps verified within 2mm target
2026-03-16 Fix 6 SUMNODE label_multiple_wires ERC warnings
    - Move 12 SUMNODE labels above next resistor pin1 (avoid wire pass-through)
    - Shorten 12 vertical wires to match new label positions
    - Remove 6 unnecessary junctions
    - ERC: 805 → 799 violations (0 errors, 799 off-grid warnings)
    - Netlist: identical (125 nets, 603 nodes, all SUMNODE nets verified)
2026-03-16 fix(sch): connect 6 ESD diode pairs — split all mid-wire pins into segments
    Each diode pair (D8/D9, D11/D12, D14/D15, D17/D18, D20/D21, D23/D24)
    had three mid-wire pin issues per pair:
    1. Internal wire spanning all 4 pins → split into 3 segments
    2. Top label wire (CHn_OUT_COLD → D_lower.A) passing through D_upper.A
    → split into 2 segments at D_upper.A
    3. Bottom GND wire (D_upper.K → GND) passing through D_lower.K
2026-03-17 FB1/FB2: Symbol von Device:L auf Device:FerriteBead geändert
    - lib_symbols Cache: Exakte Kopie aus KiCad System-Library
    - lib_id beider Instanzen aktualisiert
    - Footprint und Value bleiben: L_0805_2012Metric / BLM18PG221
    - ERC: lib_symbol_mismatch für FB1/FB2 behoben (913→911 Warnungen)
2026-03-17 PCB: GND-Via cleanup, F.Cu zone, courtyard fixes
    - 30 problematische GND-Vias entfernt (holes_co_located, hole_clearance, hole_to_hole)
    - F.Cu GND-Zone hinzugefuegt (Board-weite Massflaeche)
    - B.Cu GND-Zone mit Fill-Daten (aus KiCad GUI)
    - C38 verschoben: (143.14, 21.55) -> (143.14, 24.0) - courtyard overlap mit U15
    - C80 verschoben: (153.67, 20.32) -> (153.67, 22.0) - courtyard overlap mit Q1
    - 3 Vias entfernt (clearance violation U13, orphaned V-/GND vias)
2026-03-17 PCB: F.Cu Zone auf Solid-Connect, Zone Refill via pcbnew
    - F.Cu GND-Zone: connect_pads thermal -> solid (bessere GND-Impedanz für Audio)
    - Zone-Fill-Polygone via pcbnew Python API neu generiert + text-merged
    - DRC: 0 Errors, 0 Unconnected, 198 Warnings (alle akzeptabel)
    - Vorher: 9 starved_thermal Errors (thermal relief spokes blockiert)
2026-03-18 Production: Gerber, Drill, BOM, Position Files
    - Gerber (9 Layer): F.Cu, B.Cu, F/B.Paste, F/B.Silkscreen, F/B.Mask, Edge.Cuts
    - Drill: Excellon, mm, absolute origin
    - BOM: 263 Bauteile, 39 unique (11 Basic, 9 Extended, 19 THT)
    - Position: 269 SMD-Positionen (CSV)
    - JLCPCB-ZIP: production/aurora-dsp-icepower-booster-gerber.zip
2026-03-19 Fix: 7 eeschema ERC Errors - fehlende instances-Sektionen in 6 GND-Symbolen
    Root cause: fix_erc_all.py (vorheriger Commit) erstellte 6 GND Power-Symbole
    bei x=55mm ohne die erforderliche (instances (project ...)) Sektion.
    eeschema behandelt Symbole ohne instances als nicht-annotiert (#PWR?),
    was 6x duplicate_reference + 1x unannotated Errors verursachte.
    kicad-cli ERC erkannte diese Errors nicht (unterschiedliche Prüflogik).
    Fix: instances-Sektionen mit korrektem project-UUID und Reference
2026-03-19 fix: ESD Dioden D8/D9/D11-D15/D17-D21/D23/D24 korrekt verdrahtet
    - 18 fehlerhafte GND-Wires gelöscht (D_upper.A und D_lower.A lagen auf same GND-Wire)
    - 6 neue Wires (285,y_top)→(285,y_A_upper) für CHn_HOT_RAW → D_upper.A
    - 6 neue Labels CH{1-6}_OUT_COLD bei D_lower.A-Pin für Anode-Verbindung
    - Alle 24 ESD-Dioden jetzt korrekt: A=Signal, K=GND
    - ERC: 0 Errors (war 1 Error vor Fix), 1059 Warnings (+8 endpoint_off_grid kosmetisch)
2026-03-19 fix(readme): 📝 update functionality description and pinout details
    - Added clarification on the functionality of SW7 settings.
    - Included additional information on PESD5V0S1BL pinout for better understanding.
2026-03-19 checkpoint: pcb before resync (routing based on pre-F9/F10 schematic)
2026-03-20 fix(copilot-instructions): 📝 add rules for unconnected components in schematics and PCB
    * Ensure all components are fully connected in the schematic and PCB.
    * Add validation steps to run ERC/DRC after changes.
    * Emphasize the removal of unused components from the design.
2026-03-20 Fix Q1-Q7 SOT-23 footprint, U14 pad-net injection, exact template matching
    - Add Package_TO_SOT_SMD:SOT-23 to EXTRA_FOOTPRINTS (BSS138 is 3-pin, not 5-pin)
    - Fix template matching: exact short-name match before substring fallback
    - Fix pad-net injection for unquoted pad names (SOIC127P600X175-9N)
    - Fix outer pad regex: consume inter-group whitespace in pad block matching
    Validation: 0 ERRORS, 0 WARNINGS, 18/18 checks passed
    DRC: 0 shorts, 18 courtyard/clearance (power zone), 499 unconnected (pre-routing)
2026-03-20 Fix alle 5 Audit-Fehler: TEL5 bypass, LDO-Handling, Driver bulk caps
    Fehler 1 (U1 TEL5): C14/C15 an TEL5-Ausgangspins verschoben
    - C14 → (85, 34) = 2.2mm vom +12V_RAW Pin 14 (war 14.9mm)
    - C15 → (84.5, 19) = 2.6mm vom -12V_RAW Pin 11
    - Innerhalb U1 CrtYd — Standard-DIP-Bypass zwischen Pinreihen
    Fehler 2 (U15 LDO): Audit für LDO-Regler angepasst
    - LDOs brauchen µF-Bypass statt nF → CHECK 1 relaxiert auf 6mm bulk
2026-03-20 DRU: hv_clearance Regel fuer +24V_IN (>=0.5mm)
2026-03-21 Production-ready PCB: 0 DRC errors, library footprints, zone fill
    Major changes:
    - P1: Updated 266/268 footprints from KiCad library (larger pads)
    - P3: Fixed courtyard overlaps (C18, C79 repositioned)
    - P4: Restored all 10 suppressed DRC severity rules
    - P5: Fixed silk edge clearance, repositioned references
    - CH6: Manual route for CH6_GAIN_OUT via x=122 B.Cu detour
2026-03-22 Cleanup: Entferne 144 nicht mehr benötigte Analyse-/Debug-Skripte
    Behalte nur 20 Kern-Pipeline-Skripte:
    - Schaltplan: reformat_sch, replicate_channels
    - PCB-Aufbau: build_pcb, generate_placement, place_corrected
    - Konfiguration: configure_netclasses, add_mounting_holes
    - Routing: route_1..route_6, strip_routing, fix_dsn_classes,
    add_via_stitching_smart, dedup_vias, remove_islands_v2
2026-03-23 fix: Restore user's 3D model + silkscreen changes from backup
    Merged user's KiCad backup (2026-03-22 18:19) with J2/J15 modifications:
    - Restored custom 3D models: XLR NC3MBH, NC3FBH2, Lumberg, TEL5-2422
    - Restored XLR silkscreen line extensions (16.43→17.9, new 15.52 lines)
    - Preserved all J2/J15 footprint placements and REMOTE_IN traces
    - DRC: 0 shorts, 0 real unconnected (104 warnings: 48 silk_edge + zone fill)
2026-03-23 fix: Silkscreen-Änderungen aus Stash wiederhergestellt
    - Gain-Tabelle (F.SilkS) wiederhergestellt bei (24.892, 25.146)
    - Switch-Beschreibung (F.SilkS) wiederhergestellt bei (35.052, 23.368)
    - 'Balanced Booster' Titel verschoben nach (24.892, 197.866)
    - 'Rev 1.0' und 'Aurora DSP IcePower Booster' von B.SilkS entfernt
    - SW2 Reference-Label verschoben nach (-6.994, -4.066)
    - DRC: 0 Shorts, 0 Dangling Vias
2026-03-23 chore: DRC-Analyse-Skripte für U15 Prüfung
    - analyze_u15.py: U15 SOT-23-5 Pad-Analyse und Umgebungsprüfung
    - drc_breakdown.py: DRC-Violations nach Typ aufschlüsseln
    - find_gnd_near_u15.py: Nächste GND-Verbindungen zu U15 finden
    - Ergebnis: U15 Pad1 GND ist korrekt verbunden (Zone-Fill)
2026-03-23 fix: Netclass-Patterns mit /-Prefix für KiCad 9 Netnamen
    - Alle 27 netclass_patterns um /-Prefix ergänzt
    - GND-Pattern ohne / (KiCad power net ohne Prefix)
    - Vorher: 1/141 Netze gematchet, nachher: 128/141
    - 13 Default-Netze korrekt: 7 MOSFET-Gates + 6 Control-Signale
    - Audio_Input: 54, Audio_Output: 66, Power: 5, Audio_Power: 2, HV: 1
2026-03-23 refactor: Projekt standalone gemacht + bereinigt
    Standalone:
    - 17 System-Footprints (.kicad_mod) in footprints.pretty/ kopiert
    - 15 System-3D-Modelle (.step) in footprints.pretty/3dshapes/ kopiert
    - Alle 3D-Pfade in PCB von ${KICAD9_3DMODEL_DIR} auf ${KIPRJMOD} umgeschrieben (249 Referenzen)
    - Alle Schaltplan-Footprint-Refs von System-Libraries auf project: umgeschrieben (287 Referenzen)
    - sym-lib-table: Absoluten Pfad durch ${KIPRJMOD} ersetzt
2026-03-23 chore: 🗑️ remove unused image file
    * Deleted `IMG_8495.jpg` from the datasheets directory as it is no longer needed.
2026-03-23 docs: Rastergrafiken (PNG 300 DPI) aus SVGs generiert
    - Schematic: 3.0 MB
    - PCB Front: 917 KB
    - PCB Back: 367 KB
2026-03-23 docs: ✏️ Update README with schematic and PCB images
    * Added schematic image for better visualization of the design.
    * Included PCB front image to enhance documentation clarity.
2026-03-23 docs: 🖼️ Update 3D render images for icepower booster
    * Replaced the following images:
    - `3d-bottom.png`
    - `3d-iso.png`
    - `3d-top.png`
    * Ensured high-quality visuals for better representation of the product.
